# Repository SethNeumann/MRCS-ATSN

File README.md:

# MRCS-ATSN
### License: Creative Commons Attribution-NonCommercial-ShareAlike

## Dispatcher/Operator Telephone board / Electronic Speech Telephone Network board (ASTN)

(Designed by MRCS)

The Electronic Speech Telephone Network (ASTN) board provides the
electronics and connections for building a telephone for a Dispatcher
or Operator for use with a model railroad telephone system using
either a microphone/speaker/footswitch arrangement or using an
inexpensive computer headset.  The Mic/Speaker/Foot switch arrangement
is recommended where the dispatcher or operator will be in a
sound-isolated environment and the headset (preferably noise
cancelling) is recommended for Operators and Dispatchers who will
be in the layout room.  Features include:

  * Supports either Dynamic or Electret microphones
  * Independent control of outbound, inbound and "break-in" volume
  * Break in volume is the level heard by the user when depressing the footswitch (prototype train order operators would break in if there was an error during an order or repeat as a safety measure)
  * Can be used to "modernize" a classic candlestick type phone for better performance in a noisy layout room
  * supports mono or stereo inputs and outputs
  * optional phase reversal on output to help tune maximum volume without feedback
  * No DC load on the dispatcher's line
  * line level output for powered speakers or input to an external amplifier
  * uses 24 VDC
  * optional remote volume controls
  * transmit LED indicator

This is a Model Railroad Control Systems Telephony design by Clint Gilliland,
Seth Neumann and John Plocher.

You are free to download the files and make your own or you can
purchase bare boards or assembled and tested product from
[Model Railroad Control Systems](http://www.modelrailroadcontrolsystems.com/).

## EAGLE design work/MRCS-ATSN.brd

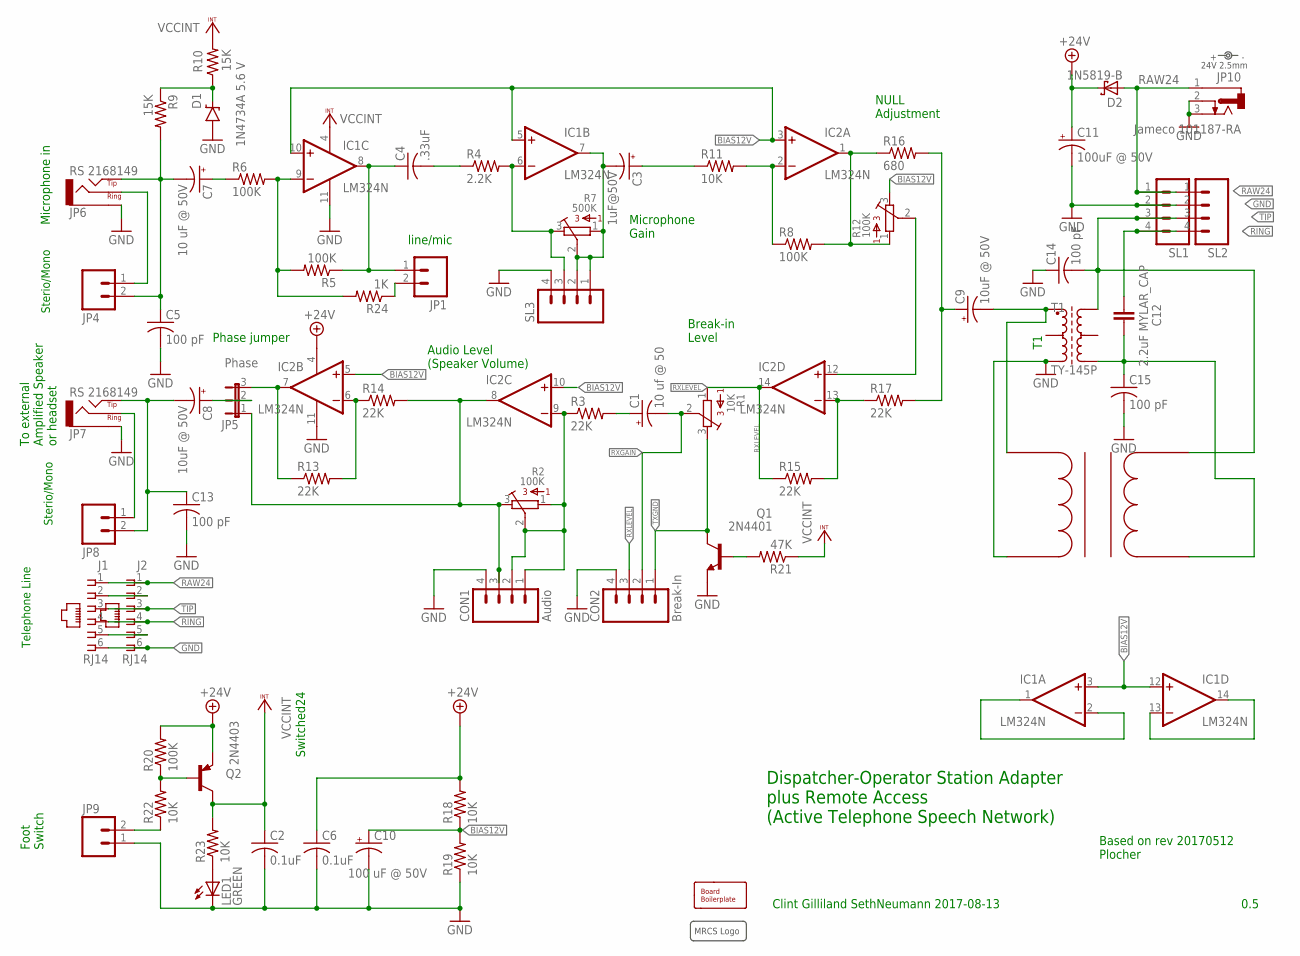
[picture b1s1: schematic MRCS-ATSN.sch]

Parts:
BOARD1: BOARD69X100; BOARD-DINRAIL-2.7IN-16CM
C1: 10 uf @ 50; E2-5
C2, C6: 0.1uF; C025-030X050
C3: 1uF@50V; E2-5
C4: .33uF; C050-050X075
C5, C13: 100 pF; C050-025X075
C7: 10 uF @ 50V; E2-5
C8, C9: 10uF @ 50V; E2-5
C10: 100 uF @ 50V; E3.5-10
C11: 100uF @ 50V; E3.5-10
C12: 2.2uF MYLAR_CAP; C15B9
C14, C15: 100 pF; C025-030X050
CON1: Audio; 1X04_LOCK
CON2: Break-In; 1X04_LOCK
D1: 1N4734A 5.6 V; DIODE-ZENER
D2: 1N5819-B; DO41-7.6
IC1, IC2: LM324N; DIL14
J1, J2: RJ14; RJ25-INVERTED
JP1, JP4, JP8: CONNECTOR-M021X02-LOCK; 1X02_LOCK
JP5: Phase; 1X03
JP6, JP7: RS 2168149; AUDIO-JACK-3.5MM_STEREO
JP9: CONNECTOR-M02508-LOCK; MSTB2
JP10: Jameco 101187-RA; DCJ0202
LED1: GREEN; LED3MM
POWER: 24V 2.5mm; POWER_USAGE
Q1: 2N4401; TO92-EBC
Q2: 2N4403; TO92-CBE
R1: 10K; 3386K
R2, R12: 100K; 3386K
R3, R13, R14, R15, R17: 22K; AXIAL-0.4
R4: 2.2K; AXIAL-0.4
R5, R6, R8, R20: 100K; AXIAL-0.4
R7: 500K; 3386K
R9, R10: 15K; AXIAL-0.4
R11, R18, R19, R22, R23: 10K; AXIAL-0.4
R16: 680; AXIAL-0.4
R21: 47K; AXIAL-0.4
R24: 1K; AXIAL-0.4
SL1, SL2, SL3: CONNECTOR-M04POLAR_LOCK; MOLEX-1X4_LOCK
T1: TY-145P; TRANFORMER
U$1: MRCS-LOGOBOT-LARGE; MRCS-LOGO
U$2: EI14_600-600; XFMR580X500

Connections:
+24V: C6.1, C11.+, D2.C, IC2.4 (V+), Q2.E, R18.P$2 (2), R20.P$2 (2)
BIAS12V: C10.+, IC1.5 (+IN), IC1.10 (+IN), IC2.3 (+IN), IC2.5 (+IN), IC2.10 (+IN), R12.3, R18.P$1 (1), R19.P$2 (2)
GND: C2.2, C5.2, C6.2, C10.-, C11.-, C13.2, C14.1, C15.2, CON1.4, CON2.4, D1.P$2 (A), IC1.11 (V-), IC2.11 (V-), J1.6, J2.6, JP6.GND (SLEEVE), JP7.GND (SLEEVE), JP9.1, JP10.2, JP10.3, LED1.K (C), Q1.E, R19.P$1 (1), SL1.2, SL2.2, SL3.4, T1.3 (E1), U$2.PBOTTOM
MICPOWER: D1.P$1 (C), R9.P$1 (1), R10.P$1 (1)
MICRING: JP4.1, JP6.RING
MICTIP: C5.1, C7.-, JP4.2, JP6.TIP, R9.P$2 (2)
unnamed: C7.+, R6.P$1 (1)
unnamed: IC1.1 (OUT), IC1.2 (-IN)
unnamed: JP1.2, R24.P$1 (1)
unnamed: IC1.3 (+IN), IC1.12 (+IN)
unnamed: Q2.B, R20.P$1 (1), R22.P$2 (2)
unnamed: IC1.9 (-IN), R5.P$2 (2), R6.P$2 (2), R24.P$2 (2)
unnamed: J1.2, J2.2
unnamed: C1.+, R3.P$2 (2)
unnamed: IC2.13 (-IN), R15.P$2 (2), R17.P$1 (1)
unnamed: J1.5, J2.5
unnamed: C3.-, IC1.7 (OUT), R7.1, R7.2, SL3.1, SL3.2
unnamed: IC2.2 (-IN), R8.P$1 (1), R11.P$2 (2)
unnamed: IC2.1 (OUT), R8.P$2 (2), R12.1, R16.P$1 (1)
unnamed: JP9.2, R22.P$1 (1)
unnamed: C3.+, R11.P$1 (1)
unnamed: C4.1, IC1.8 (OUT), JP1.1, R5.P$1 (1)
unnamed: CON1.1, CON1.2, IC2.9 (-IN), R2.1, R2.2, R3.P$1 (1)
unnamed: LED1.A, R23.P$1 (1)
unnamed: IC2.12 (+IN), R12.2
unnamed: IC1.13 (-IN), IC1.14 (OUT)
unnamed: C8.+, JP5.2
unnamed: IC1.6 (-IN), R4.P$2 (2), R7.3, SL3.3
unnamed: C4.2, R4.P$1 (1)
unnamed: CON1.3, IC2.8 (OUT), JP5.1, R2.3, R14.P$2 (2)
unnamed: IC2.7 (OUT), JP5.3, R13.P$1 (1)
unnamed: IC2.6 (-IN), R13.P$2 (2), R14.P$1 (1)
Q1BASE: Q1.B, R21.P$2 (2)
RAW24: D2.A, J1.1, J2.1, JP10.1, SL1.1, SL2.1
RING: C12.2, J1.4, J2.4, SL1.4, SL2.4
RING-ISOLATED: C12.1, C15.1, T1.4 (E2), U$2.SBOTTOM
RXGAIN: C1.-, CON2.2, R1.2
RXLEVEL: CON2.3, IC2.14 (OUT), R1.1, R15.P$1 (1)
SPKRRING: JP7.RING, JP8.1
SPKRTIP: C8.-, C13.1, JP7.TIP, JP8.2
TELCO-IN: C9.-, T1.1 (A1), U$2.PTOP
TELCO-IN-ISOLATED: C9.+, R16.P$2 (2), R17.P$2 (2)
TIP: C14.2, J1.3, J2.3, SL1.3, SL2.3, T1.6 (A2), U$2.STOP
TXGND: CON2.1, Q1.C, R1.3
VCCINT: C2.1, IC1.4 (V+), Q2.C, R10.P$2 (2), R21.P$1 (1), R23.P$2 (2)

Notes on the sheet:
Dispatcher-Operator Station Adapter plus Remote Access (Active Telephone Speech Network)
Clint Gilliland SethNeumann 2017-08-13
To external Amplified Speaker or headset
Microphone in
Foot Switch
NULL Adjustment
Microphone Gain
Phase jumper
Break-in Level
Sterio/Mono
Telephone Line
Based on rev 20170512 Plocher
Switched24
Audio Level (Speaker Volume)
0.5
line/mic

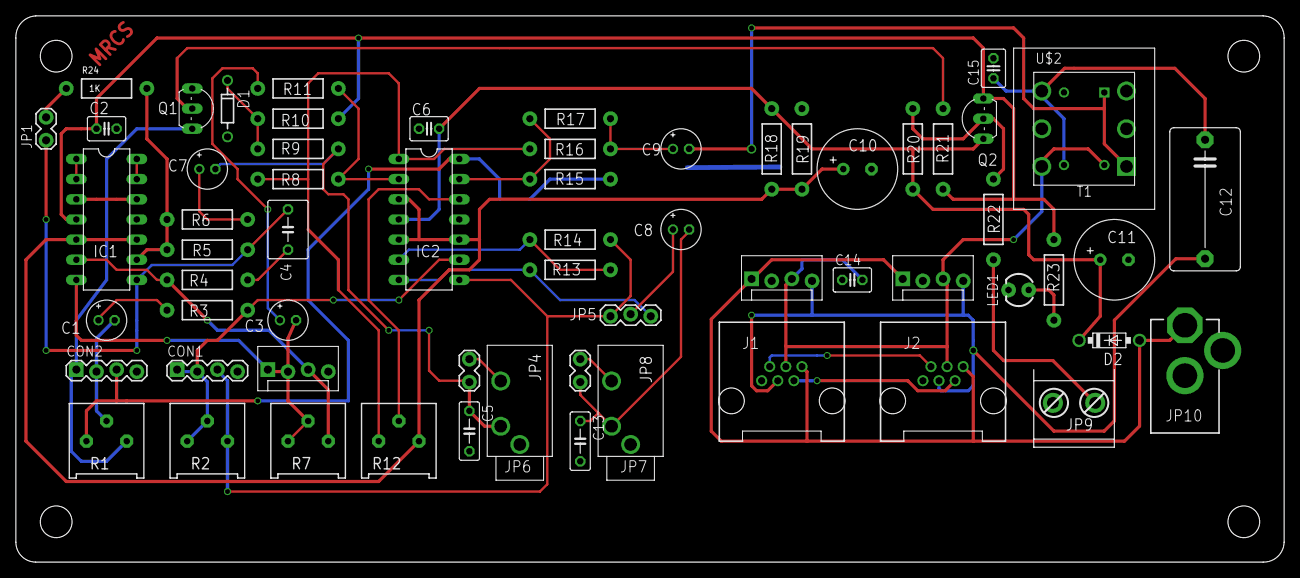
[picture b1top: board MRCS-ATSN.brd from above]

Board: 2 copper layers, 159.8 x 68.8 mm, 66 parts (0 on the bottom side), 45 nets.

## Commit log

2019-11-28 ensured License is CC-NC-SA
2020-10-05 added missing values
2022-05-10 clean up of messy import

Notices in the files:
parts and their libraries:
SparkFun-Aesthetics: Licensing: CC v3.0 Share-Alike You are welcome to use this library for commercial purposes.
SparkFun-DiscreteSemi: Licensing: Creative Commons ShareAlike 4.0 International - https://creativecommons.org/licenses/by-sa/4.0
